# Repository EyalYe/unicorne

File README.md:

# unicorne

A unibody [Corne](https://github.com/foostan/crkbd): both halves of the Corne v3 key layout on one PCB, each half
rotated 16°, with an Azoteq TPS43 trackpad in the middle (it sits on the case, over the nice!nano) and a nice!nano v2 at the top.

Status: layout fixed, schematic done, MX and Choc boards fully routed (DRC: 0 unconnected, 0 copper violations).

## Design

- 42 keys (3×6 + 3 thumbs per half), outer pinky columns break off for a 36-key board
- Key spacing, stagger, thumb cluster and LED positions copied from crkbd `v3-final` (19.0 mm pitch)
- Two board versions with the same placement: Kailh MX hotswap, and Kailh Choc hotswap (fits Choc V1 and V2)
- nice!nano v2 on the top side, components up, USB on the top edge; the edge is notched for the
  mid-mount USB-C, whose shell drops below the nano's underside
- TPS43 trackpad wired to six bare pads (no FPC, to keep it thin). It sits on the case above the board, so it
  may cover the nice!nano; its position is the one that brings the halves closest together (higher and it
  meets the inner columns' top keycaps, lower and the thumb keycaps). It is drawn on F.Fab and User.Drawings
  only, with no 3D model on the board
- Optional LEDs: 12 SK6812MINI underglow + 42 SK6812MINI-E per key, on their own MOSFET-switched supply.
  A solder jumper picks the source: the nice!nano's 3.3 V VCC (up to its 1 A regulator), or an external
  supply up to 5 V on the LED IN pads for full brightness. Never the battery.
- MSK-12C02 battery cut-off switch, through-hole battery pads
- Exposed pads: expansion header (3V3, GND, UART, I2C) and GPIO header (P0.24, P1.00, P0.11)
- Pro Micro mode: a Pro Micro-footprint controller without the nice!nano's three inner pins (P1.01, P1.02,
  P1.07) works with three solder jumpers bridged, which move those nets to outer pins that aren't the Pro
  Micro I2C pair:

  | Jumper | Net (nice!nano pin) | Bridged to | That pin's other use, lost in this mode |
  |---|---|---|---|
  | JP4 | COL5 (P1.01) | P0.24 | free GPIO / sensor MISO |
  | JP5 | COL6 (P1.02) | P0.11 | free GPIO / sensor CS |
  | JP6 | ROW5 (P1.07) | P0.08 | UART RX |

  I2C (SDA/SCL), the trackpad's RDY, LED data (P0.06) and LED power (P1.00) keep working. Leave all three
  open with a nice!nano, or two controller pins drive one net. In firmware, point COL5, COL6 and ROW5 at the
  bridged pins.

The full pin plan and parts list are in `mock/index.html` (open it in a browser).

## Parts list

Everything is hand-soldered. Quantities are for one board; the 36-key build needs 36 of each per-key part.

### On the PCB

| Ref | Qty | Part | Footprint | Notes |
|---|---|---|---|---|
| U1 | 1 | nice!nano v2 | through-hole, top side | Needs the 3 inner pads (P1.01, P1.02, P1.07) too; use low-profile sockets or solder directly |
| SW1–42 | 42 | Key switches: MX, or Choc V1/V2 | hotswap | MX on `unicorne.kicad_pcb`, Choc on `unicorne-choc.kicad_pcb` |
| — | 42 | Hotswap sockets: Kailh MX, or Kailh Choc | SMD, bottom | The Choc socket fits both V1 and V2 switches |
| D1–42 | 42 | 1N4148W diode | SOD-123, bottom | |
| SW43 | 1 | MSK-12C02 slide switch | SMD, bottom, top edge | Battery cut-off |
| SW44 | 1 | TS-1136 H4.3 tactile switch (6.0×3.5 mm, 4.3 mm tall, 2 pins) | through-hole, top, beside the nano | Reset |
| J1 | — | Battery B+ / B− pads | through-hole, 4.8 mm | Solder the battery leads here |
| J2 | — | TPS43 pads | through-hole, 2.54 mm | Wires to the trackpad (trackpad build) |
| J5 | — | Sensor pads | through-hole, 2.54 mm | Wires to a PAW3395 / PMW3360 board (sensor build) |
| J3 | 1 | 1×6 pin header, 2.54 mm | through-hole | Optional: expansion (3V3, GND, UART, I2C) |
| J4 | 1 | 1×4 pin header, 2.54 mm | through-hole | Optional: GPIO (P0.24, P1.00, P0.11) |
| R3, R4 | 2 | 4.7 kΩ resistor | 0603 hand-solder | Trackpad build only (I2C pull-ups); leave off with a sensor |
| R5 | 1 | 10 kΩ resistor | 0603 hand-solder | Trackpad / sensor reset pull-up |

### Optional LEDs

Leave all of these off for a board without lighting.

| Ref | Qty | Part | Footprint | Notes |
|---|---|---|---|---|
| LED1–12 | 12 | SK6812MINI | 3.5 mm PLCC4, bottom | Underglow |
| LED13–54 | 42 | SK6812MINI-E | reverse mount, bottom | Per-key; shines up through a cutout |
| JP2 | — | 3-pad solder jumper | — | LED source: bridge VCC–centre, or EXT–centre for J6 |
| J6 | — | LED IN pads (V+, GND) | through-hole, 2.54 mm | External LED supply up to 5 V, e.g. a USB-C breakout; only with JP2 on EXT |
| Q1 | 1 | AO3401A P-MOSFET | SOT-23 | Switches the LED supply |
| Q2 | 1 | 2N7002 N-MOSFET | SOT-23 | Driven by P1.00 |
| R1, R2 | 2 | 100 kΩ resistor | 0603 hand-solder | Keep the LEDs off during boot |
| C1 | 1 | 10 µF capacitor | 0603 hand-solder | LED supply |
| U2 | 1 | SN74LV1T125 buffer | SOT-23-5 hand-solder | LED data level shifter, needed only with JP2 on EXT; must be the LV1T (not 74LVC1G125) so 3.3 V data works at 5 V |
| C2 | 1 | 100 nF capacitor | 0603 hand-solder | U2 decoupling; leave off with U2 |
| JP3 | — | Solder jumper | — | U2 bypass: bridge it with JP2 on VCC and U2 left off |
| JP1 | — | Solder jumper | — | Bridge it to send LED data from P0.06 (through U2) |
| JP4–JP6 | — | Solder jumpers | — | Pro Micro mode only: bridge all three without a nice!nano; open with one |

### Off the PCB

| Qty | Part | Notes |
|---|---|---|
| 1 | Azoteq TPS43 trackpad (43.3 × 40.3 mm) | Trackpad build; or a PAW3395 / PMW3360 sensor board for a trackball (3.3 V supply) |
| 1 | 3.7 V LiPo battery | Sits under the trackpad on the bottom; size it to your case |
| 42 | Keycaps, MX or Choc | 40 × 1u and 2 × 1.5u (the big thumb key on each half) |
| 10 | M2 button-head screws (ISO 7380) + standoffs | Mounting holes H1–H10; standoff height depends on the case |

## Ordering (JLCPCB)

Upload `export/jlcpcb/unicorne-mx-jlcpcb.zip` or `unicorne-choc-jlcpcb.zip` (gerbers plus Excellon drills,
plated and non-plated separate). Settings:

| Option | Value |
|---|---|
| Layers | 2 |
| Thickness | 1.6 mm |
| Size | about 293 × 119 mm (read from the outline) |
| Min. via / hole | 0.3 mm via drill, 0.5 mm mouse-bite holes |
| Min. track / spacing | 0.2 mm / 0.2 mm (0.15 mm rule minimum) |
| Surface finish | HASL (lead-free if you prefer) |
| Everything else | defaults |

No assembly: every part is hand-soldered (see the parts list). Regenerate the zips with
`python3 tools/export_gerbers.py` after any board change; it refuses to export a board that fails DRC.

## 3D

`export/unicorne-mx.step` and `export/unicorne-choc.step` are the full boards with parts, for designing a
case (rendered previews next to them). Sockets and the Cherry MX and Choc V1 switches are real models; the nice!nano,
TPS43, SK6812MINI and MSK-12C02 are size-accurate placeholder boxes from `tools/step_box.py`.
Regenerate with `python3 tools/export_3d.py` after any board change.

## Switch plates

The top plate, as a starting point for a case. Plates are solid (no break lines), so there is one per
switch type and size:

| Plate | Cutouts | Thickness |
|---|---|---|
| `plate/unicorne-mx-42-plate.kicad_pcb`, `plate/unicorne-mx-36-plate.kicad_pcb` | 14.0 mm | 1.5 mm |
| `plate/unicorne-choc-42-plate.kicad_pcb`, `plate/unicorne-choc-36-plate.kicad_pcb` | 13.8 mm | 1.2 mm |

Each has the same outline, coordinates and M2 holes as its PCB, a 44.3 x 41.3 mm opening for the TPS43,
an opening over the nice!nano that runs out through the top edge (so the USB stays reachable) and a window
over the reset switch, both with 0.5 mm clearance.
The 36-key plates are cut evenly on both sides where the PCB snaps off its outer columns (on Choc, whose
break lines differ by side, at their average), with rounded corners.
`export/plate/` holds, per plate:

- `*-jlcpcb.zip`: order as an FR4 board, no copper (the copper layers are included empty so JLCPCB's
  viewer reads the stack); set the thickness above.
- `*.dxf`: Edge.Cuts outline in mm, for laser-cut aluminium, steel or acrylic.
- `*.step`: the plate solid, in the same coordinates as the board STEP files.
- `*.png`: a render.

## Files

| Path | Contents |
|---|---|
| `unicorne.kicad_pro` | KiCad 10 project |
| `unicorne.kicad_sch`, `matrix.kicad_sch`, `leds.kicad_sch` | Schematic (generated, see below) |
| `unicorne.kicad_pcb` | MX hotswap PCB (generated, see below) |
| `unicorne-choc.kicad_pcb`, `unicorne-choc.kicad_pro` | Choc V1/V2 hotswap PCB, same placement |
| `unicorne.kicad_dru` | Extra DRC rules (LED cutout edge clearance) |
| `lib/` | Project symbols and footprints; third-party credits in `lib/ATTRIBUTION.md` |
| `tools/fp_tactile.py` | Generates the reset switch footprint |
| `tools/layout.py` | Key, trackpad and outline geometry → `mock/layout.json`, `mock/unicorne.svg` |
| `tools/gen_schematic.py` | Generates the schematic sheets from `mock/layout.json` |
| `tools/gen_pcb.py` | Builds both PCBs from the schematic netlist and `mock/layout.json` |
| `tools/krt_route.py` | Routes a freshly generated board (used for both boards): fixed lanes, then [KiCadRoutingTools](https://github.com/drandyhaas/KiCadRoutingTools) 0.23.7 for every other signal at standard JLCPCB sizes with no via in or next to a pad, the maze router for anything left, GND pours and stitching, then its plane repair. Expects KiCadRoutingTools in `~/Development/tools/KiCadRoutingTools` with its own venv |
| `tools/finish_route.py` | The older all-in-house router: fixed lanes, then KiCad's ratsnest with the maze router, GND pours and stitching; up to 10 attempts, then GND repair and stub cleanup. Also keeps new vias out of pads |
| `tools/gnd_repair.py` | Finds GND copper the pours left cut off and joins it (a via, or rip-up and reroute of whatever boxes it in) |
| `tools/lanes.py`, `tools/maze_route.py` | Fixed routing lanes for the key grid; the grid A* router |
| `tools/route.py` | Freerouting driver (not used for the final boards) |
| `tools/step_box.py`, `lib/3d/` | Placeholder STEP models and the socket / Choc switch models |
| `tools/export_3d.py`, `export/` | STEP export of both boards, and 3D renders |
| `tools/export_gerbers.py`, `export/jlcpcb/` | JLCPCB gerber + drill zips |
| `docs/led-map.md`, `docs/led-map.csv` | Every LED's index in the data chain (0-based, for firmware), its reference, spot and the key's matrix row and column |
| `tools/led_map.py` | Generates the LED map from the board |
| `tools/led_order.json` | The LED chain order, picked in the LED Chain Order page; `gen_schematic.py` uses it when present |
| `tools/waves.py` | Wavy silkscreen pattern on both sides of the routed PCBs |
| `tools/gen_plate.py`, `plate/`, `export/plate/` | 42- and 36-key switch plates and their exports |
| `mock/` | Layout data, a 1:1 printable SVG and the design overview page |

## Regenerating

```sh
# Geometry (needs KiCad's bundled Python for the outline)
/Applications/KiCad/KiCad.app/Contents/Frameworks/Python.framework/Versions/Current/bin/python3 tools/layout.py

# Schematic (overwrites the three .kicad_sch files)
python3 tools/gen_schematic.py

# PCBs (overwrite the board files; placement, outline, holes, silkscreen, no tracks)
# then route them; both steps throw away any hand routing
/Applications/KiCad/KiCad.app/Contents/Frameworks/Python.framework/Versions/Current/bin/python3 tools/gen_pcb.py mx
/Applications/KiCad/KiCad.app/Contents/Frameworks/Python.framework/Versions/Current/bin/python3 tools/gen_pcb.py choc
/Applications/KiCad/KiCad.app/Contents/Frameworks/Python.framework/Versions/Current/bin/python3 tools/krt_route.py mx
/Applications/KiCad/KiCad.app/Contents/Frameworks/Python.framework/Versions/Current/bin/python3 tools/krt_route.py choc
# On MX the plane repair reaches U2 pad 3 (GND, boxed in by LED_DIN) only through a via in the
# pad, which krt_route.py removes, leaving that pad unconnected. The committed board joins it by
# hand: a via at (160.65, 137.45) between pads 3 and 4, a back-layer track to pad 3 and a
# front-layer track to the GND copper.

# LED map for firmware (chain index -> LED, switch, matrix position)
/Applications/KiCad/KiCad.app/Contents/Frameworks/Python.framework/Versions/Current/bin/python3 tools/led_map.py

# Wavy silkscreen on both PCBs (redraws only the waves, leaves the routing alone)
/Applications/KiCad/KiCad.app/Contents/Frameworks/Python.framework/Versions/Current/bin/python3 tools/waves.py

# Switch plates and their exports (reads hole positions from the routed boards)
/Applications/KiCad/KiCad.app/Contents/Frameworks/Python.framework/Versions/Current/bin/python3 tools/gen_plate.py
```

## Licenses

The nice!nano footprint comes from [bstiq/nice-nano-kicad](https://github.com/bstiq/nice-nano-kicad) under GPLv3;
the hotswap footprints from [keyswitch-kicad-library](https://github.com/joe-scotto/keyswitch-kicad-library) under MIT.

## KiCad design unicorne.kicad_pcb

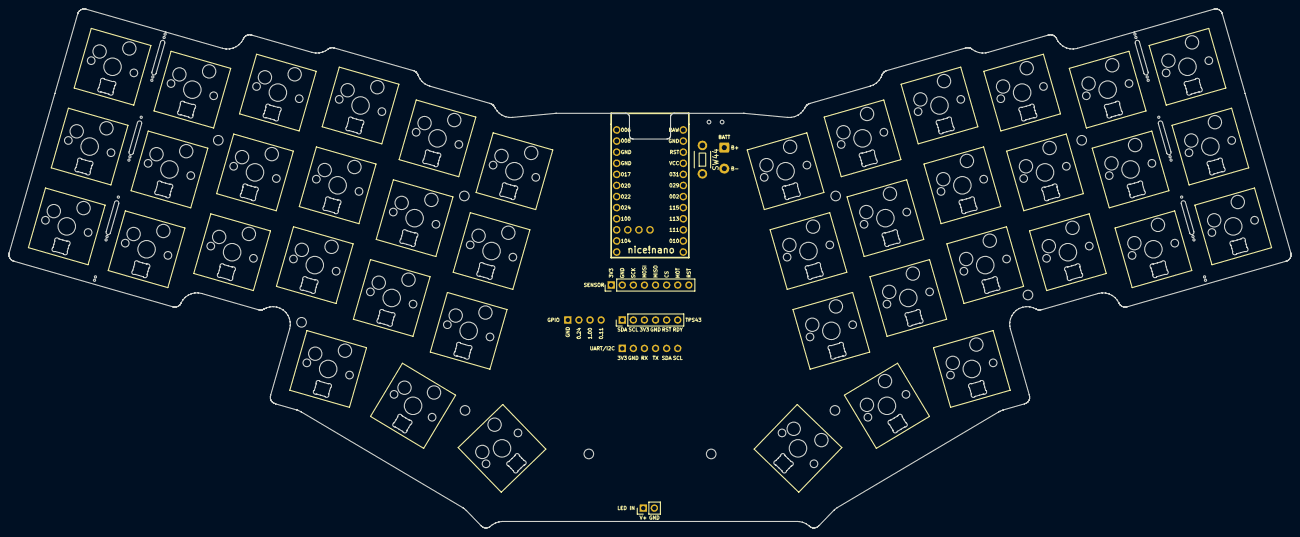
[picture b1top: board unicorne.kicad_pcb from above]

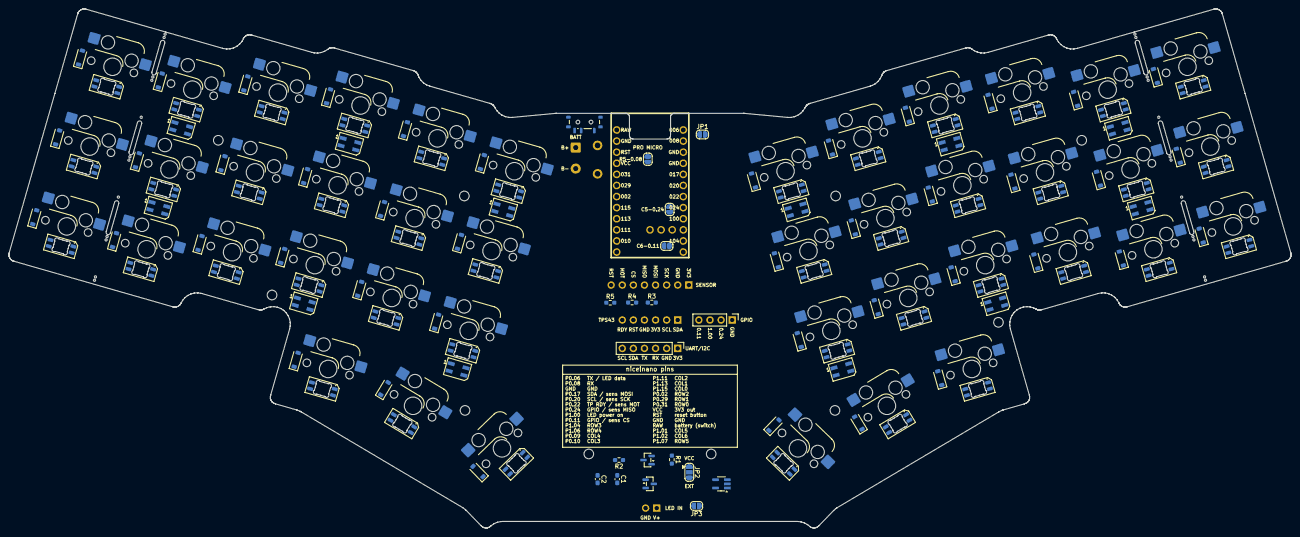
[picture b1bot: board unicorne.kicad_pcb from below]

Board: 2 copper layers, 293.4 x 118.8 mm, 175 parts (116 on the bottom side), 128 nets, no tracks yet.

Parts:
C1: 10uF; C_0603_1608Metric_Pad1.08x0.95mm_HandSolder
C2: 100nF; C_0603_1608Metric_Pad1.08x0.95mm_HandSolder
D1, D2, D3, D4, D5, D6, D7, D8, D9, D10, D11, D12, D13, D14, D15, D16, D17, D18, D19, D20, D21, D22, D23, D24, D25, D26, D27, D28, D29, D30, D31, D32, D33, D34, D35, D36, D37, D38, D39, D40, D41, D42: 1N4148W; D_SOD-123
H1, H2, H3, H4, H5, H6, H7, H8, H9, H10: M2; MountingHole_2.2mm_M2_ISO7380
J1: Battery; SolderWire-0.5sqmm_1x02_P4.8mm_D0.9mm_OD2.3mm
J2: TPS43; PinHeader_1x06_P2.54mm_Vertical
J3: Expansion; PinHeader_1x06_P2.54mm_Vertical
J4: GPIO; PinHeader_1x04_P2.54mm_Vertical
J5: PAW3395 / PMW3360; PinHeader_1x08_P2.54mm_Vertical
J6: LED power in; PinHeader_1x02_P2.54mm_Vertical
JP1: LED data; SolderJumper-2_P1.3mm_Open_RoundedPad1.0x1.5mm
JP2: LED source; SolderJumper-3_P1.3mm_Open_RoundedPad1.0x1.5mm
JP3: U2 bypass; SolderJumper-2_P1.3mm_Open_RoundedPad1.0x1.5mm
JP4: COL5 to P0.24; SolderJumper-2_P1.3mm_Open_RoundedPad1.0x1.5mm
JP5: COL6 to P0.11; SolderJumper-2_P1.3mm_Open_RoundedPad1.0x1.5mm
JP6: ROW5 to P0.08; SolderJumper-2_P1.3mm_Open_RoundedPad1.0x1.5mm
LED1, LED2, LED3, LED5, LED6, LED7, LED9, LED10, LED12, LED14, LED15, LED16, LED17, LED19, LED20, LED21, LED22, LED24, LED25, LED27, LED28, LED30, LED31, LED32, LED33, LED34, LED35, LED36, LED38, LED39, LED41, LED42, LED43, LED44, LED46, LED48, LED49, LED50, LED51, LED52, LED53, LED54: SK6812MINI-E; LED_SK6812MINI-E_3.2x2.8mm_P1.5mm_ReverseMount
LED4, LED8, LED11, LED13, LED18, LED23, LED26, LED29, LED37, LED40, LED45, LED47: SK6812MINI; LED_SK6812MINI_PLCC4_3.5x3.5mm_P1.75mm
MB1, MB2: mouse bites
Q1: AO3401A; SOT-23
Q2: 2N7002; SOT-23
R1, R2: 100k; R_0603_1608Metric_Pad0.98x0.95mm_HandSolder
R3, R4: 4.7k; R_0603_1608Metric_Pad0.98x0.95mm_HandSolder
R5: 10k; R_0603_1608Metric_Pad0.98x0.95mm_HandSolder
SW1: R0C0; SW_Hotswap_Kailh_MX_1.00u
SW2: R0C1; SW_Hotswap_Kailh_MX_1.00u
SW3: R0C2; SW_Hotswap_Kailh_MX_1.00u
SW4: R0C3; SW_Hotswap_Kailh_MX_1.00u
SW5: R0C4; SW_Hotswap_Kailh_MX_1.00u
SW6: R0C5; SW_Hotswap_Kailh_MX_1.00u
SW7: R1C0; SW_Hotswap_Kailh_MX_1.00u
SW8: R1C1; SW_Hotswap_Kailh_MX_1.00u
SW9: R1C2; SW_Hotswap_Kailh_MX_1.00u
SW10: R1C3; SW_Hotswap_Kailh_MX_1.00u
SW11: R1C4; SW_Hotswap_Kailh_MX_1.00u
SW12: R1C5; SW_Hotswap_Kailh_MX_1.00u
SW13: R2C0; SW_Hotswap_Kailh_MX_1.00u
SW14: R2C1; SW_Hotswap_Kailh_MX_1.00u
SW15: R2C2; SW_Hotswap_Kailh_MX_1.00u
SW16: R2C3; SW_Hotswap_Kailh_MX_1.00u
SW17: R2C4; SW_Hotswap_Kailh_MX_1.00u
SW18: R2C5; SW_Hotswap_Kailh_MX_1.00u
SW19: R0C6; SW_Hotswap_Kailh_MX_1.00u
SW20: R1C6; SW_Hotswap_Kailh_MX_1.00u
SW21: R2C6; SW_Hotswap_Kailh_MX_1.50u
SW22: R3C0; SW_Hotswap_Kailh_MX_1.00u
SW23: R3C1; SW_Hotswap_Kailh_MX_1.00u
SW24: R3C2; SW_Hotswap_Kailh_MX_1.00u
SW25: R3C3; SW_Hotswap_Kailh_MX_1.00u
SW26: R3C4; SW_Hotswap_Kailh_MX_1.00u
SW27: R3C5; SW_Hotswap_Kailh_MX_1.00u
SW28: R4C0; SW_Hotswap_Kailh_MX_1.00u
SW29: R4C1; SW_Hotswap_Kailh_MX_1.00u
SW30: R4C2; SW_Hotswap_Kailh_MX_1.00u
SW31: R4C3; SW_Hotswap_Kailh_MX_1.00u
SW32: R4C4; SW_Hotswap_Kailh_MX_1.00u
SW33: R4C5; SW_Hotswap_Kailh_MX_1.00u
SW34: R5C0; SW_Hotswap_Kailh_MX_1.00u
SW35: R5C1; SW_Hotswap_Kailh_MX_1.00u
SW36: R5C2; SW_Hotswap_Kailh_MX_1.00u
SW37: R5C3; SW_Hotswap_Kailh_MX_1.00u
SW38: R5C4; SW_Hotswap_Kailh_MX_1.00u
SW39: R5C5; SW_Hotswap_Kailh_MX_1.00u
SW40: R3C6; SW_Hotswap_Kailh_MX_1.00u
SW41: R4C6; SW_Hotswap_Kailh_MX_1.00u
SW42: R5C6; SW_Hotswap_Kailh_MX_1.50u
SW43: Power; SW_SPDT_Shouhan_MSK12C02
SW44: Reset; SW_Tactile_SPST_3.5x6mm_H4.3mm_THT
U1: nice!nano v2; nice_nano
U2: SN74LV1T125; SOT-23-5_HandSoldering

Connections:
+3V3: J2.3, J3.1, J5.1, JP2.1, R3.1, R4.1, R5.1, U1.21
/BATT+: J1.1, SW43.2
/LED_DATA: JP1.2, JP3.1, U2.2
/LED_EN: J4.3, Q2.1, R2.1, U1.9
/LED_EN_N: Q1.1, Q2.3, R1.2
/LED_EXT: J6.1, JP2.3
/LED_SRC: JP2.2, Q1.2, R1.1
/LEDs/LED_D1: LED1.4, LED2.2
/LEDs/LED_D2: LED2.4, LED3.2
/LEDs/LED_D3: LED3.4, LED4.3
/LEDs/LED_D4: LED4.1, LED5.2
/LEDs/LED_D5: LED5.4, LED6.2
/LEDs/LED_D6: LED6.4, LED7.2
/LEDs/LED_D7: LED7.4, LED8.3
/LEDs/LED_D8: LED8.1, LED9.2
/LEDs/LED_D9: LED9.4, LED10.2
/LEDs/LED_D10: LED10.4, LED11.3
/LEDs/LED_D11: LED11.1, LED12.2
/LEDs/LED_D12: LED12.4, LED13.3
/LEDs/LED_D13: LED13.1, LED14.2
/LEDs/LED_D14: LED14.4, LED15.2
/LEDs/LED_D15: LED15.4, LED16.2
/LEDs/LED_D16: LED16.4, LED17.2
/LEDs/LED_D17: LED17.4, LED18.3
/LEDs/LED_D18: LED18.1, LED19.2
/LEDs/LED_D19: LED19.4, LED20.2
/LEDs/LED_D20: LED20.4, LED21.2
/LEDs/LED_D21: LED21.4, LED22.2
/LEDs/LED_D22: LED22.4, LED23.3
/LEDs/LED_D23: LED23.1, LED24.2
/LEDs/LED_D24: LED24.4, LED25.2
/LEDs/LED_D25: LED25.4, LED26.3
/LEDs/LED_D26: LED26.1, LED27.2
/LEDs/LED_D27: LED27.4, LED28.2
/LEDs/LED_D28: LED28.4, LED29.3
/LEDs/LED_D29: LED29.1, LED30.2
/LEDs/LED_D30: LED30.4, LED31.2
/LEDs/LED_D31: LED31.4, LED32.2
/LEDs/LED_D32: LED32.4, LED33.2
/LEDs/LED_D33: LED33.4, LED34.2
/LEDs/LED_D34: LED34.4, LED35.2
/LEDs/LED_D35: LED35.4, LED36.2
/LEDs/LED_D36: LED36.4, LED37.3
/LEDs/LED_D37: LED37.1, LED38.2
/LEDs/LED_D38: LED38.4, LED39.2
/LEDs/LED_D39: LED39.4, LED40.3
/LEDs/LED_D40: LED40.1, LED41.2
/LEDs/LED_D41: LED41.4, LED42.2
/LEDs/LED_D42: LED42.4, LED43.2
/LEDs/LED_D43: LED43.4, LED44.2
/LEDs/LED_D44: LED44.4, LED45.3
/LEDs/LED_D45: LED45.1, LED46.2
/LEDs/LED_D46: LED46.4, LED47.3
/LEDs/LED_D47: LED47.1, LED48.2
/LEDs/LED_D48: LED48.4, LED49.2
/LEDs/LED_D49: LED49.4, LED50.2
/LEDs/LED_D50: LED50.4, LED51.2
/LEDs/LED_D51: LED51.4, LED52.2
/LEDs/LED_D52: LED52.4, LED53.2
/LEDs/LED_D53: LED53.4, LED54.2
/NRST: J2.5, J5.8, R5.2
/P0.06: J3.4, JP1.1, U1.1
/P0.08: J3.3, JP6.2, U1.2
/P0.11_CS: J4.4, J5.6, JP5.2, U1.10
/P0.24_MISO: J4.2, J5.5, JP4.2, U1.8
/RDY_MOTION: J2.6, J5.7, U1.7
/RST: SW44.1, U1.22
/SCL_SCK: J2.2, J3.6, J5.3, R4.2, U1.6
/SDA_MOSI: J2.1, J3.5, J5.4, R3.2, U1.5
/VBAT: SW43.1, U1.24
COL0: SW1.1, SW7.1, SW13.1, SW22.1, SW28.1, SW34.1, U1.17
COL1: SW2.1, SW8.1, SW14.1, SW23.1, SW29.1, SW35.1, U1.16
COL2: SW3.1, SW9.1, SW15.1, SW24.1, SW30.1, SW36.1, U1.15
COL3: SW4.1, SW10.1, SW16.1, SW25.1, SW31.1, SW37.1, U1.14
COL4: SW5.1, SW11.1, SW17.1, SW26.1, SW32.1, SW38.1, U1.13
COL5: JP4.1, SW6.1, SW12.1, SW18.1, SW27.1, SW33.1, SW39.1, U1.31
COL6: JP5.1, SW19.1, SW20.1, SW21.1, SW40.1, SW41.1, SW42.1, U1.32
GND: C1.2, C2.2, J1.2, J2.4, J3.2, J4.1, J5.2, J6.2, LED1.1, LED2.1, LED3.1, LED4.2, LED5.1, LED6.1, LED7.1, LED8.2, LED9.1, LED10.1, LED11.2, LED12.1, LED13.2, LED14.1, LED15.1, LED16.1, LED17.1, LED18.2, LED19.1, LED20.1, LED21.1, LED22.1, LED23.2, LED24.1, LED25.1, LED26.2, LED27.1, LED28.1, LED29.2, LED30.1, LED31.1, LED32.1, LED33.1, LED34.1, LED35.1, LED36.1, LED37.2, LED38.1, LED39.1, LED40.2, LED41.1, LED42.1, LED43.1, LED44.1, LED45.2, LED46.1, LED47.2, LED48.1, LED49.1, LED50.1, LED51.1, LED52.1, LED53.1, LED54.1, Q2.2, R2.2, SW44.2, U1.3, U1.4, U1.23, U2.1, U2.3
LED_DIN: JP3.2, LED1.2, U2.4
LED_VDD: C1.1, C2.1, LED1.3, LED2.3, LED3.3, LED4.4, LED5.3, LED6.3, LED7.3, LED8.4, LED9.3, LED10.3, LED11.4, LED12.3, LED13.4, LED14.3, LED15.3, LED16.3, LED17.3, LED18.4, LED19.3, LED20.3, LED21.3, LED22.3, LED23.4, LED24.3, LED25.3, LED26.4, LED27.3, LED28.3, LED29.4, LED30.3, LED31.3, LED32.3, LED33.3, LED34.3, LED35.3, LED36.3, LED37.4, LED38.3, LED39.3, LED40.4, LED41.3, LED42.3, LED43.3, LED44.3, LED45.4, LED46.3, LED47.4, LED48.3, LED49.3, LED50.3, LED51.3, LED52.3, LED53.3, LED54.3, Q1.3, U2.5
unnamed: D1.2, SW1.2
unnamed: D2.2, SW2.2
unnamed: D3.2, SW3.2
unnamed: D4.2, SW4.2
unnamed: D5.2, SW5.2
unnamed: D6.2, SW6.2
unnamed: D7.2, SW7.2
unnamed: D8.2, SW8.2
unnamed: D9.2, SW9.2
unnamed: D10.2, SW10.2
unnamed: D11.2, SW11.2
unnamed: D12.2, SW12.2
unnamed: D13.2, SW13.2
unnamed: D14.2, SW14.2
unnamed: D15.2, SW15.2
unnamed: D16.2, SW16.2
unnamed: D17.2, SW17.2
unnamed: D18.2, SW18.2
unnamed: D19.2, SW19.2
unnamed: D20.2, SW20.2
unnamed: D21.2, SW21.2
unnamed: D22.2, SW22.2
unnamed: D23.2, SW23.2
unnamed: D24.2, SW24.2
unnamed: D25.2, SW25.2
unnamed: D26.2, SW26.2
unnamed: D27.2, SW27.2
unnamed: D28.2, SW28.2
unnamed: D29.2, SW29.2
unnamed: D30.2, SW30.2
unnamed: D31.2, SW31.2
unnamed: D32.2, SW32.2
unnamed: D33.2, SW33.2
unnamed: D34.2, SW34.2
unnamed: D35.2, SW35.2
unnamed: D36.2, SW36.2
unnamed: D37.2, SW37.2
unnamed: D38.2, SW38.2
unnamed: D39.2, SW39.2
unnamed: D40.2, SW40.2
unnamed: D41.2, SW41.2
unnamed: D42.2, SW42.2
ROW0: D1.1, D2.1, D3.1, D4.1, D5.1, D6.1, D19.1, U1.20
ROW1: D7.1, D8.1, D9.1, D10.1, D11.1, D12.1, D20.1, U1.19
ROW2: D13.1, D14.1, D15.1, D16.1, D17.1, D18.1, D21.1, U1.18
ROW3: D22.1, D23.1, D24.1, D25.1, D26.1, D27.1, D40.1, U1.11
ROW4: D28.1, D29.1, D30.1, D31.1, D32.1, D33.1, D41.1, U1.12
ROW5: D34.1, D35.1, D36.1, D37.1, D38.1, D39.1, D42.1, JP6.1, U1.33

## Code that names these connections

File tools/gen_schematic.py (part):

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    jp3.connect(1, "LED_DATA")
    jp3.connect(2, "LED_DIN")
    # Pro Micro compatibility: a controller with only the 24 outer pins has no
    # P1.01 / P1.02 / P1.07, so these move COL5, COL6 and ROW5 onto outer pins that
    # aren't the Pro Micro I2C pair (SDA/SCL stay free, as do RDY, LED data and LED_EN)
    for ref, a, b_, y in (("JP4", "COL5", "P0.24_MISO", 172.72), ("JP5", "COL6", "P0.11_CS", 182.88),
                          ("JP6", "ROW5", "P0.08", 193.04)):
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    c2.connect(2, "GND")
    root.text("LED supply: bridge JP2 A-C for VCC (3.3 V, up to the regulator's 1 A) or B-C for J6\n"
              "(external supply up to 5 V, for full brightness). Never from the battery: RAW is the\n"
              "charger's battery pin. Q1 switches it onto LED_VDD when P1.00 (LED_EN) is high;\n"
              "R1/R2 keep it off during boot. ZMK: ext-power on P1.00, VCC kept on by a gpio-hog.\n"
              "Close JP1 to drive the LEDs from P0.06. U2 shifts the data level for a 5 V supply;\n"
              "with VCC, leave U2 and C2 off and bridge JP3 instead.", 27.94, 142.24)
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    # ---- root: trackpad
    j2 = root.symbol("Connector_Generic:Conn_01x06", "J2", "TPS43", 307.34, 50.8, footprint=FP["trackpad"], in_bom=False,
                     fields={"Note": "Bare pads for wires to the TPS43, in the module's pad order"})
    for pin, net in enumerate(["SDA_MOSI", "SCL_SCK", "+3V3", "GND", "NRST", "RDY_MOTION"], 1):
        j2.connect(pin, net)
    for ref, val, net, x in (("R3", "4.7k", "SDA_MOSI", 335.28), ("R4", "4.7k", "SCL_SCK", 350.52),
                             ("R5", "10k", "NRST", 365.76)):
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    j5 = root.symbol("Connector_Generic:Conn_01x08", "J5", "PAW3395 / PMW3360", 307.34, 165.1,
                     footprint=FP["sensor"], in_bom=False,
                     fields={"Note": "Bare pads for a PAW3395 or PMW3360 sensor board, used instead of the trackpad"})
    for pin, net in enumerate(["+3V3", "GND", "SCL_SCK", "SDA_MOSI", "P0.24_MISO", "P0.11_CS",
                               "RDY_MOTION", "NRST"], 1):
        j5.connect(pin, net)
    root.text("J5: optical sensor (PAW3395 / PMW3360) instead of the trackpad, over SPI:\n"
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
    # ---- root: exposed headers
    j3 = root.symbol("Connector_Generic:Conn_01x06", "J3", "Expansion", 307.34, 101.6, footprint=FP["hdr6"])
    for pin, net in enumerate(["+3V3", "GND", "P0.08", "P0.06", "SDA_MOSI", "SCL_SCK"], 1):
        j3.connect(pin, net)
    j4 = root.symbol("Connector_Generic:Conn_01x04", "J4", "GPIO", 307.34, 132.08, footprint=FP["hdr4"])
    for pin, net in enumerate(["GND", "P0.24_MISO", "LED_EN", "P0.11_CS"], 1):
        j4.connect(pin, net)
    root.text("J3 expansion: UART on P0.08/P0.06, I2C shared with the trackpad.\n"
              "J4 GPIO: P0.24 and P0.11 (sensor MISO/CS if J5 is used); P1.00 is LED_EN.", 292.1, 142.24)

    # ---- root: power flags and sub-sheets
    for i, net in enumerate(["GND", "VBAT", "LED_VDD", "BATT+", "LED_EXT"]):
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        led.connect("DOUT", nxt)
        prev = nxt
    leds.text("Chain: left underglow, left rows (left to right), left thumbs, right thumbs, right rows,\n"
              "right underglow, then the breakable outer pinky columns (right, then left). LED_VDD powers all.",
              25.4, 254.0)

    matrix.path = f"/{root.uuid}/{matrix.uuid}"
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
